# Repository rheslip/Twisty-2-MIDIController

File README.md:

# Twisty 2 MIDI Controller
2nd Generation of my Twisty MIDI controller using Raspberry Pi Pico or Pico 2.

The Twisty 2 MIDI controller has 16 parameter encoders with switches, 16 RGB LEDs, 2 menu encoders, 128x32 pixel OLED display, USB MIDI, TRS MIDI Out, and optional Bluetooth MIDI with Pico W or Pico 2W.
It provides four pages of MIDI controls and fully customizable MIDI messages, encoder ranges, switch functions and LED colors for each control. Text labels can be attached to each control as a visual aid to what the control does. You can save and recall up to 16 controller setups in the Pico's flash memory. STL files for a 3D printed case are provided as well.

Twisty 2 is a completely open source project - source code, KICad schematics and layout, gerber files and enclosure 3D files are in this archive.

Video Overview: https://youtu.be/-W1Gd_hKzS8

Jan 13/2026 - switched MIDI interfaces so they all use the Control Surface library and cleaned up the MIDI interface names - BLE MIDI note on/off works now. Fixed a bug in the init code. 

Jan 25/2026 - added code for a Moog SubHarmonicon like sequencer using the Twisty 2 hardware:

https://www.youtube.com/watch?v=RM_LAcxyHQQ

https://github.com/rheslip/Twisty-2-MIDIController/tree/main/source/Twisty2_Rhythmicon

**Build Guide**

Solder the .1u caps, resistors and the diode. Solder the 16 SK6812 RGB leds making sure the orientation is correct and that the LEDs face the top side of the PCB. Solder the TRS MIDI out jack.

Solder the TSSOP 74HC4067s. I apply a very thin layer of flux to the pads and place the chip so its aligned on the pads. Using a fine tipped soldering iron tack one pin down with solder, adjust as needed and when the part is correctly aligned tack another pin down. Make sure the pins are sitting flat on the pads before you solder the rest. Solder each pin with very fine solder and don't worry about shorts between pins. Once all the pins are soldered examine your work with a magnifier and remove any shorts beween pins with fine solder wick.

Clip the support lugs off all the encoders - there was not enough room in the layout to accomodate them. The encoders have good mechanical support from the enclosure top anyway. The encoders mount from the TOP side of the board and are soldered on the bottom side. You **MUST** solder S2, S6, D2 and D6 **BEFORE** mounting the Pico board. Soldering S2, S6 and then the Pico makes soldering the Pico somewhat easier than soldering all the encoders first.

After all the encoders are soldered, mount the OLED display - temporarily mount the enclosure top as a guide to get the spacing from the display to the top correct.

Hardest part of the build is soldering the three TSSOP 74HC4067 analog MUXes. If encoders aren't working, recheck the soldering on these chips - most faults will be here! Rest of the build is straightforward.

Pico can be mounted with header strips. I used header pins in the corners and short wires to connect the Pico to the PCB which makes the Pico board a lot easier to remove if needed.

Side view of OLED mounting

**Enclosure**

The prototype enclosure was printed on a Bambu P1S with black PLA+ filament. For the most part the stock filament settings were used. Slowing down the first layer speeds by 50% helps with adhesion and finish if you are using a textured build plate. The light pipe holes in the top had to be drilled a bit to fit 1.75mm transparent PETG which was lightly glued to hold it in place. Use small screws to attach the PCB to the standoffs in the enclosure bottom. Slide the enclosure top over the encoder shafts and hold it in place with encoder nuts.

**User Guide**

The top 16 controls (control=encoder+switch) are used to send MIDI CC messages, program change messages or or note on/off messages depending on how the controls are configured. The two extra controls at the bottom are used in conjunction with the OLED display to configure controls, save configurations and recall configurations.

The RGB LEDs associated with each control normally show the state of whatever was last used - encoder as a color and switch states as off or bright white. Encoder LED brightness changes as the control is moved to give a relative idea of the encoder setting. Double click the bottom left control to toggle between showing encoder states and switch states.

Rotate bottom left encoder to move between the 4 pages of controls. Default colors for each page are Red (page 1), Orange (page 2), Green (page ) and Aqua (page 4).

The top line of the OLED display shows the current page, the last used control, its message type and MIDI channel. The larger text below that shows a label if one has been configured and the last value that was sent for that control.

**The Configuration Menu**

Clicking the bottom left control will bring up a configuration menu to edit the last control that was used. The LED for that control will flash to indicate it is selected for editing. To select a different control when in edit mode either press a control switch to choose it or use bottom left encoder to scroll to a different control on the current page.

When in edit mode use the bottom right encoder the scroll through the edit menu items. Click the bottom right control switch to select an item - a "*" character will appear beside the item to indicate it is being edited. Use the bottom right encoder to change the value for the item and click the bottom right encoder switch to select a value.

Click the bottom left encoder again to exit the configuration edit menu.

**Configuration Menu Items:**

**Enc MIDI Ch.** - selects the MIDI channel that the selected encoder will send CC messages on

**Enc CC No.**  - selects the CC number for this encoder. The default CC assignments are 16-31 for page 1, 32-47 for page 2, 48-63 for page 3 and 64-79 for page 4

**Enc Label** - default is "CC". There are approximately 100 common audio terms (e.g. "Level", "Filter", "Track"...) that can be selected as an aid for remembering the function of the control. The label will be displayed instead of the CC number whenever this encoder is used.

**Enc Color** - selects the LED color for this encoder - Red, Orange, Green, Aqua, Blue or Violet. This is useful for grouping control functions by color.

**Enc Min** - minimum CC value that will be sent when the encoder is rotated - defaults to 0

**Enc Max** - maximum CC value that will be sent when the encoder is rotated - defaults to 127. 
**Note** If the minimum setting is higher than the maximum the encoder will reverse ie rotating clockwise sends a lower CC value.

**Switch MIDI Ch.** - selects the MIDI channel that the selected switch will send CC messages on

**Switch Mode** - selects either momentary mode (press for max value, release for min value) or toggle mode (select min or max value on alternate presses)

**Switch Type** - selects switch function:

     **CC** = send CC messages 
 
     **PC** = send program change messages
 
     **Note** = send Note on/off messages
 
     **SetEnc** = when the switch is activated, set the associated encoder on this control to Maxvalue. This provides a quick way to set an encoder to a specific value e.g. set a filter to flat response.
 
**Switch CC No.** - selects the CC number for this switch. This selection only applies when the switch type is send CC messages. The default switch CC assignments are the same as the associated encoder but on MIDI channel 2. 

**Switch Label** - same as encoder label - a memory aid for what the switch does

**Switch Min** - CC, PC or note value sent when the switch changes to its inactive state. defaults to 0

**Switch Max** - CC, PC or note value sent when the switch changes to its active state. defaults to 127. When switch type is SetEnc, sets associated encoder to this value.

**The Save/Load Menu**

Clicking the bottom right encoder enters the save/load menu. Twisty 2 supports saving and loading up to 16 different configurations in the Pico's flash memory.

**Note** You must select an FS size in the Arduino Pico Tools menu - 128K or larger is suggested. The application will automatically format a new FS if it has not been used before. Internally the application uses the LittleFS filesystem and stores configurations as JSON files.

**Save/Load Menu Items:**

**Slot** - selects the slot number 1-16 to save the current configuration to.

**Action** - select Load to load an already saved configuration from the selected slot. Save will save the current configuration to the selected slot. Format will reformat the LittleFS partition - this will ERASE ALL previously saved configurations.

**Confirm** - select Yes to confirm the selected action. The app will **NOT** warn you if you are about to overwrite an existing configuration. If Yes is selected the requested action will be performed, a success/fail message will appear and the Save/load Menu will exit.

**Note** You will get an error message if you attempt to load a configuration slot that hasn't previously been saved to.

To exit the Save/Load menu without changing anything click the bottom left control switch.

**Building the Firmware**

The app was written in Arduino 2.3.7 with the Pico Arduino board support package installed. Select the board type as Pico, Pico 2, Pico 2 or Pico 2W depending on the board you used. The prototype was tested with both a Pico W and a Pico 2 W. In the tools menu select the FS size you want (128k or more is recommended), IP/Bluetooth stack as IPV4 + Bluetooth if you want BLE MIDI, and select the USB stack as Adafruit TinyUSB. This app should not need overclocking since the CPU demands are light.

If you want BLE MIDI, use a Pico W or Pico 2W and uncomment the #define BLUETOOTH directive near the top of the main source file.

Note: I used the Control Surface library because it was the only one I could find that supports BLE MIDI for Arduino Pico. It will give you a warning about supported platforms when you compile but the library does work on the RP2040 and RP2350.

**Library Dependencies**

Adafruit Graphics

Adafruit SSD1306 driver

Adafruit TinyUSB

Adafruit NeoPixel

Arduino MIDI

Arduino JSON  https://arduinojson.org/

Control Surface  https://github.com/tttapa/Control-Surface

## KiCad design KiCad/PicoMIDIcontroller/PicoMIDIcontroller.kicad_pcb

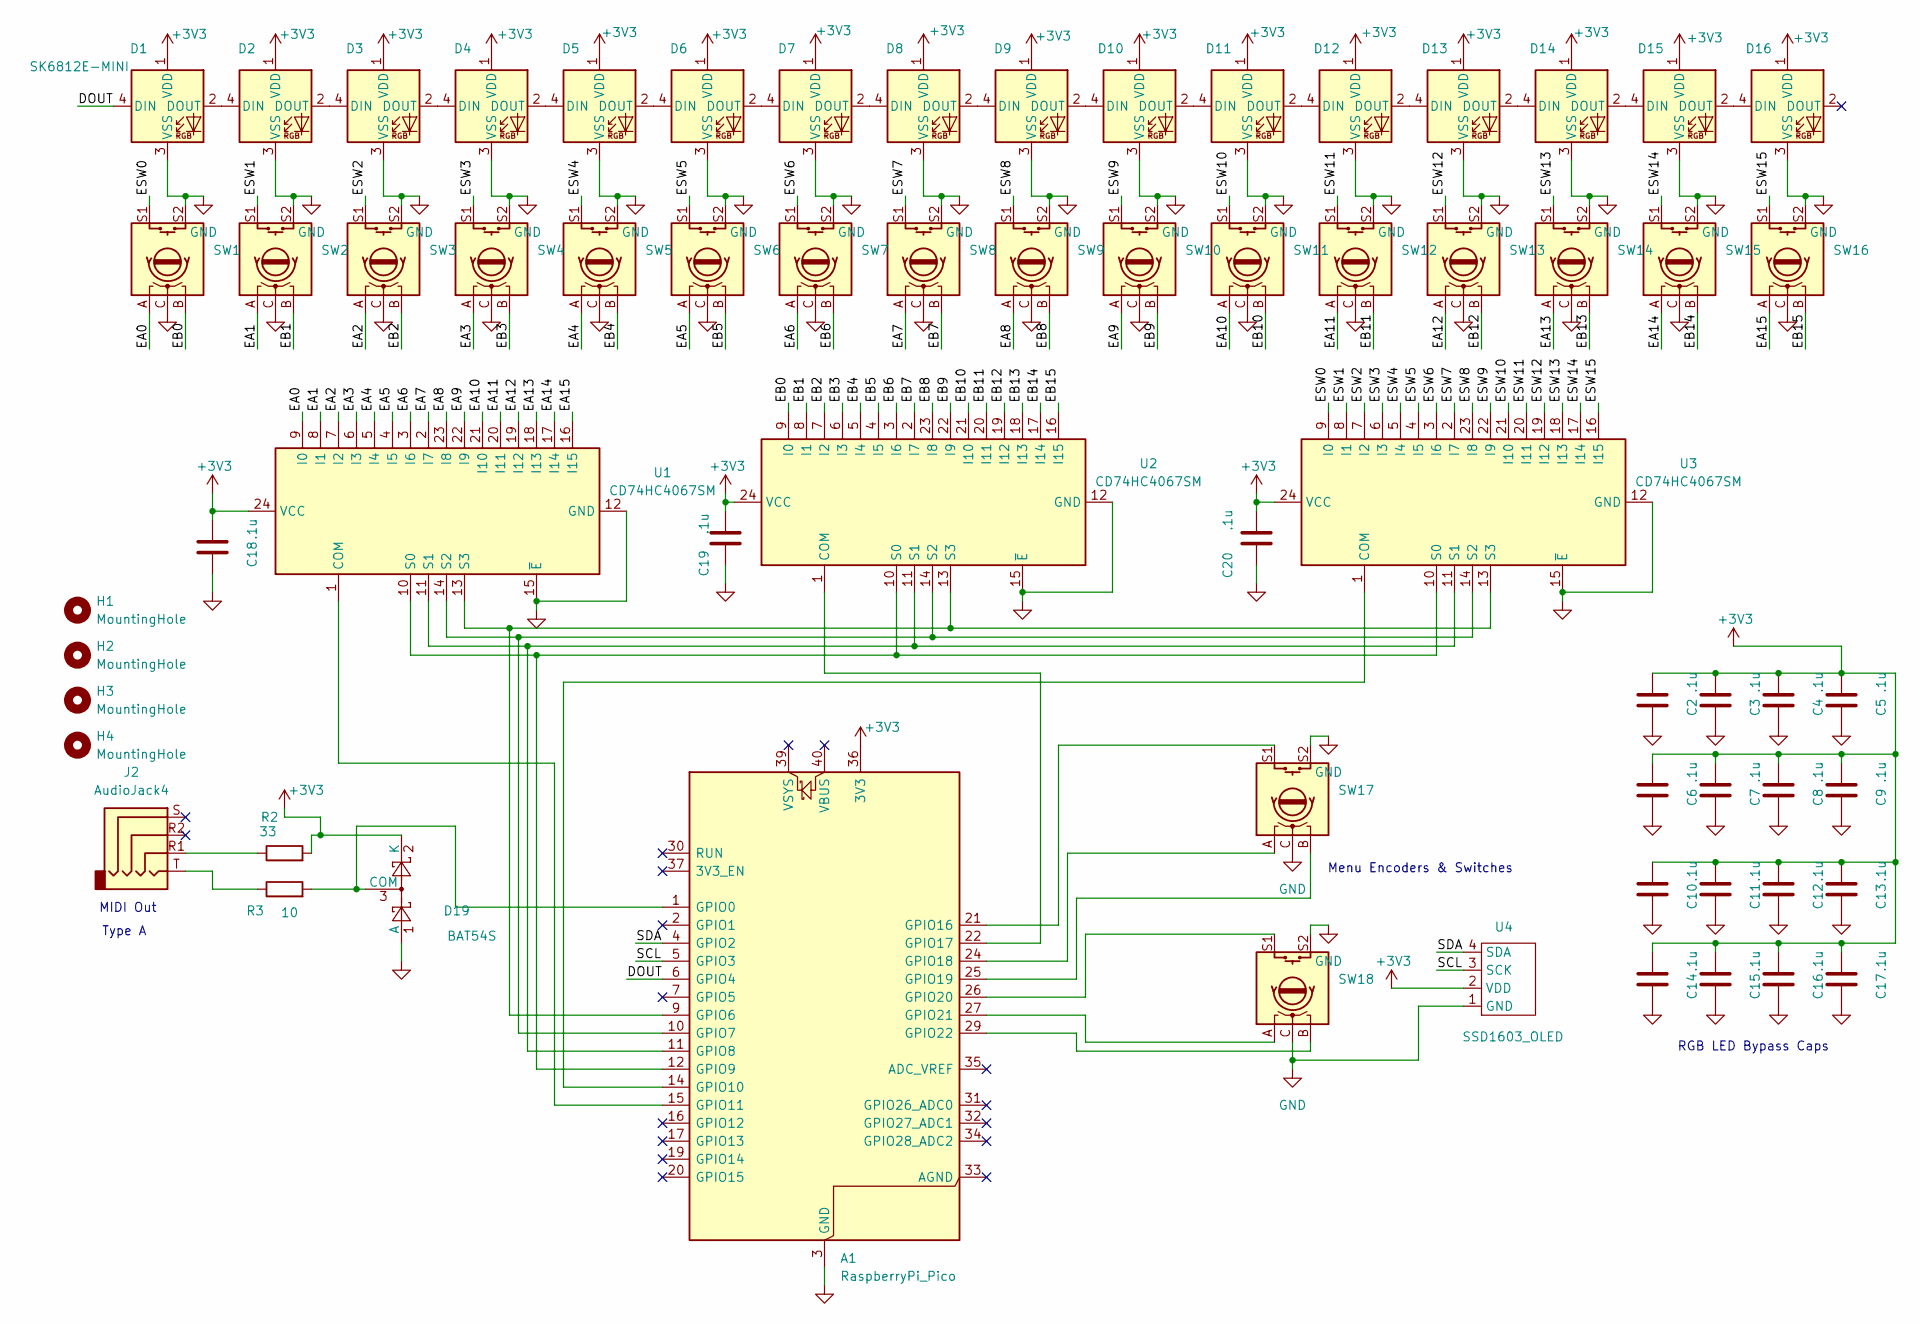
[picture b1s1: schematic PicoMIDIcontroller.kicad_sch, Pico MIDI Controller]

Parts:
A1: RaspberryPi_Pico; RaspberryPi_Pico_Common_nokeepout
C2, C3, C4, C5, C6, C7, C8, C9, C10, C11, C12, C13, C14, C15, C16, C17, C18, C19, C20: .1u; C_0603_1608Metric_Pad1.08x0.95mm_HandSolder
D1, D2, D3, D4, D5, D6, D7, D8, D9, D10, D11, D12, D13, D14, D15, D16: SK6812E-MINI; LED_OPSCO_SK6812_MINI-E_5.0x5.0mm_P3.1mm_rearmount
D19: BAT54S; SOT-23
H1, H2, H3, H4: MountingHole; MountingHole_3.2mm_M3
J2: AudioJack4; Jack_3.5mm_KoreanHropartsElec_PJ-320D-4A_Horizontal
R2: 33; R_0603_1608Metric_Pad0.98x0.95mm_HandSolder
R3: 10; R_0603_1608Metric_Pad0.98x0.95mm_HandSolder
SW1, SW2, SW3, SW4, SW5, SW6, SW7, SW8, SW9, SW10, SW11, SW12, SW13, SW14, SW15, SW16, SW17, SW18: RotaryEncoder_Switch; RotaryEncoder_Alps_EC11E-Switch_Vertical_H20mm_topsolder
U1, U2, U3: CD74HC4067SM; SSOP-24_5.3x8.2mm_P0.65mm
U4: SSD1603_OLED; PinHeader_1x04_P2.54mm_Vertical

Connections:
+3V3: A1.36 (3V3), C2.2, C3.2, C4.2, C5.2, C6.2, C7.2, C8.2, C9.2, C10.2, C11.2, C12.2, C13.2, C14.2, C15.2, C16.2, C17.2, C18.2, C19.2, C20.2, D1.1 (VDD), D2.1 (VDD), D3.1 (VDD), D4.1 (VDD), D5.1 (VDD), D6.1 (VDD), D7.1 (VDD), D8.1 (VDD), D9.1 (VDD), D10.1 (VDD), D11.1 (VDD), D12.1 (VDD), D13.1 (VDD), D14.1 (VDD), D15.1 (VDD), D16.1 (VDD), D19.2 (K), R2.2, U1.24 (VCC), U2.24 (VCC), U3.24 (VCC), U4.2 (VDD); also elsewhere on the board
/DOUT: A1.6 (GPIO4), D1.4 (DIN); also elsewhere on the board
/EA0: SW1.A, U1.9 (I0)
/EA1: SW2.A, U1.8 (I1)
/EA2: SW3.A, U1.7 (I2)
/EA3: SW4.A, U1.6 (I3)
/EA4: SW5.A, U1.5 (I4)
/EA5: SW6.A, U1.4 (I5)
/EA6: SW7.A, U1.3 (I6)
/EA7: SW8.A, U1.2 (I7)
/EA8: SW9.A, U1.23 (I8)
/EA9: SW10.A, U1.22 (I9)
/EA10: SW11.A, U1.21 (I10)
/EA11: SW12.A, U1.20 (I11)
/EA12: SW13.A, U1.19 (I12)
/EA13: SW14.A, U1.18 (I13)
/EA14: SW15.A, U1.17 (I14)
/EA15: SW16.A, U1.16 (I15)
/EB0: SW1.B, U2.9 (I0)
/EB1: SW2.B, U2.8 (I1)
/EB2: SW3.B, U2.7 (I2)
/EB3: SW4.B, U2.6 (I3)
/EB4: SW5.B, U2.5 (I4)
/EB5: SW6.B, U2.4 (I5)
/EB6: SW7.B, U2.3 (I6)
/EB7: SW8.B, U2.2 (I7)
/EB8: SW9.B, U2.23 (I8)
/EB9: SW10.B, U2.22 (I9)
/EB10: SW11.B, U2.21 (I10)
/EB11: SW12.B, U2.20 (I11)
/EB12: SW13.B, U2.19 (I12)
/EB13: SW14.B, U2.18 (I13)
/EB14: SW15.B, U2.17 (I14)
/EB15: SW16.B, U2.16 (I15)
/ESW0: SW1.S1, U3.9 (I0)
/ESW1: SW2.S1, U3.8 (I1)
/ESW2: SW3.S1, U3.7 (I2)
/ESW3: SW4.S1, U3.6 (I3)
/ESW4: SW5.S1, U3.5 (I4)
/ESW5: SW6.S1, U3.4 (I5)
/ESW6: SW7.S1, U3.3 (I6)
/ESW7: SW8.S1, U3.2 (I7)
/ESW8: SW9.S1, U3.23 (I8)
/ESW9: SW10.S1, U3.22 (I9)
/ESW10: SW11.S1, U3.21 (I10)
/ESW11: SW12.S1, U3.20 (I11)
/ESW12: SW13.S1, U3.19 (I12)
/ESW13: SW14.S1, U3.18 (I13)
/ESW14: SW15.S1, U3.17 (I14)
/ESW15: SW16.S1, U3.16 (I15)
/SCL: A1.5 (GPIO3), U4.3 (SCK); also elsewhere on the board
/SDA: A1.4 (GPIO2), U4.4 (SDA); also elsewhere on the board
GND: A1.3 (GND), A1.8 (GND), A1.13 (GND), A1.18 (GND), A1.23 (GND), A1.28 (GND), A1.38 (GND), C2.1, C3.1, C4.1, C5.1, C6.1, C7.1, C8.1, C9.1, C10.1, C11.1, C12.1, C13.1, C14.1, C15.1, C16.1, C17.1, C18.1, C19.1, C20.1, D1.3 (VSS), D2.3 (VSS), D3.3 (VSS), D4.3 (VSS), D5.3 (VSS), D6.3 (VSS), D7.3 (VSS), D8.3 (VSS), D9.3 (VSS), D10.3 (VSS), D11.3 (VSS), D12.3 (VSS), D13.3 (VSS), D14.3 (VSS), D15.3 (VSS), D16.3 (VSS), D19.1 (A), SW1.C, SW1.S2, SW2.C, SW2.S2, SW3.C, SW3.S2, SW4.C, SW4.S2, SW5.C, SW5.S2, SW6.C, SW6.S2, SW7.C, SW7.S2, SW8.C, SW8.S2, SW9.C, SW9.S2, SW10.C, SW10.S2, SW11.C, SW11.S2, SW12.C, SW12.S2, SW13.C, SW13.S2, SW14.C, SW14.S2, SW15.C, SW15.S2, SW16.C, SW16.S2, SW17.C, SW17.S2, SW18.C, SW18.S2, U1.12 (GND), U1.15 (~E), U2.12 (GND), U2.15 (~E), U3.12 (GND), U3.15 (~E), U4.1 (GND); also elsewhere on the board
unnamed 53: A1.1 (GPIO0), D19.3 (COM), R3.2; also elsewhere on the board
unnamed 54: A1.9 (GPIO6), U1.13 (S3), U2.13 (S3), U3.13 (S3); also elsewhere on the board
unnamed 55: A1.10 (GPIO7), U1.14 (S2), U2.14 (S2), U3.14 (S2); also elsewhere on the board
unnamed 56: A1.11 (GPIO8), U1.11 (S1), U2.11 (S1), U3.11 (S1); also elsewhere on the board
unnamed 57: A1.12 (GPIO9), U1.10 (S0), U2.10 (S0), U3.10 (S0); also elsewhere on the board
unnamed 58: A1.14 (GPIO10), U3.1 (COM); also elsewhere on the board
unnamed 59: A1.15 (GPIO11), U1.1 (COM); also elsewhere on the board
unnamed 60: A1.21 (GPIO16), SW17.S1; also elsewhere on the board
unnamed 61: A1.22 (GPIO17), U2.1 (COM); also elsewhere on the board
unnamed 62: A1.24 (GPIO18), SW17.A; also elsewhere on the board
unnamed 63: A1.25 (GPIO19), SW17.B; also elsewhere on the board
unnamed 64: A1.26 (GPIO20), SW18.S1; also elsewhere on the board
unnamed 65: A1.27 (GPIO21), SW18.A; also elsewhere on the board
unnamed 66: A1.29 (GPIO22), SW18.B; also elsewhere on the board
unnamed: D1.2 (DOUT), D2.4 (DIN)
unnamed: D2.2 (DOUT), D3.4 (DIN)
unnamed: D3.2 (DOUT), D4.4 (DIN)
unnamed: D4.2 (DOUT), D5.4 (DIN)
unnamed: D5.2 (DOUT), D6.4 (DIN)
unnamed: D6.2 (DOUT), D7.4 (DIN)
unnamed: D7.2 (DOUT), D8.4 (DIN)
unnamed: D8.2 (DOUT), D9.4 (DIN)
unnamed: D9.2 (DOUT), D10.4 (DIN)
unnamed: D10.2 (DOUT), D11.4 (DIN)
unnamed: D11.2 (DOUT), D12.4 (DIN)
unnamed: D12.2 (DOUT), D13.4 (DIN)
unnamed: D13.2 (DOUT), D14.4 (DIN)
unnamed: D14.2 (DOUT), D15.4 (DIN)
unnamed: D15.2 (DOUT), D16.4 (DIN)
unnamed: J2.R1, R2.1
unnamed: J2.T, R3.1

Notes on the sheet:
MIDI Out
RGB LED Bypass Caps
Menu Encoders & Switches
Type A

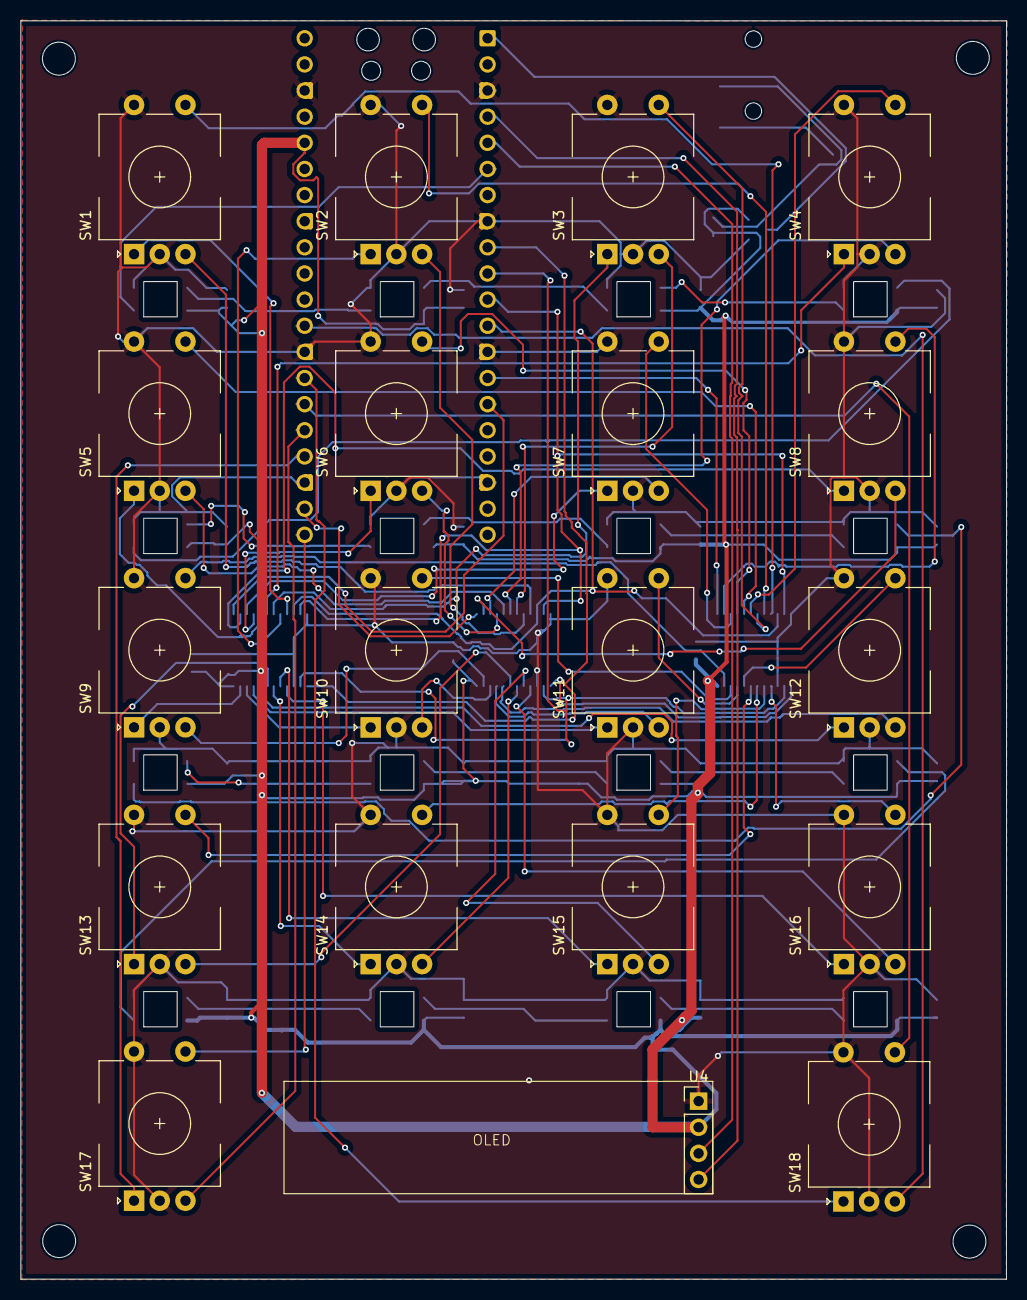
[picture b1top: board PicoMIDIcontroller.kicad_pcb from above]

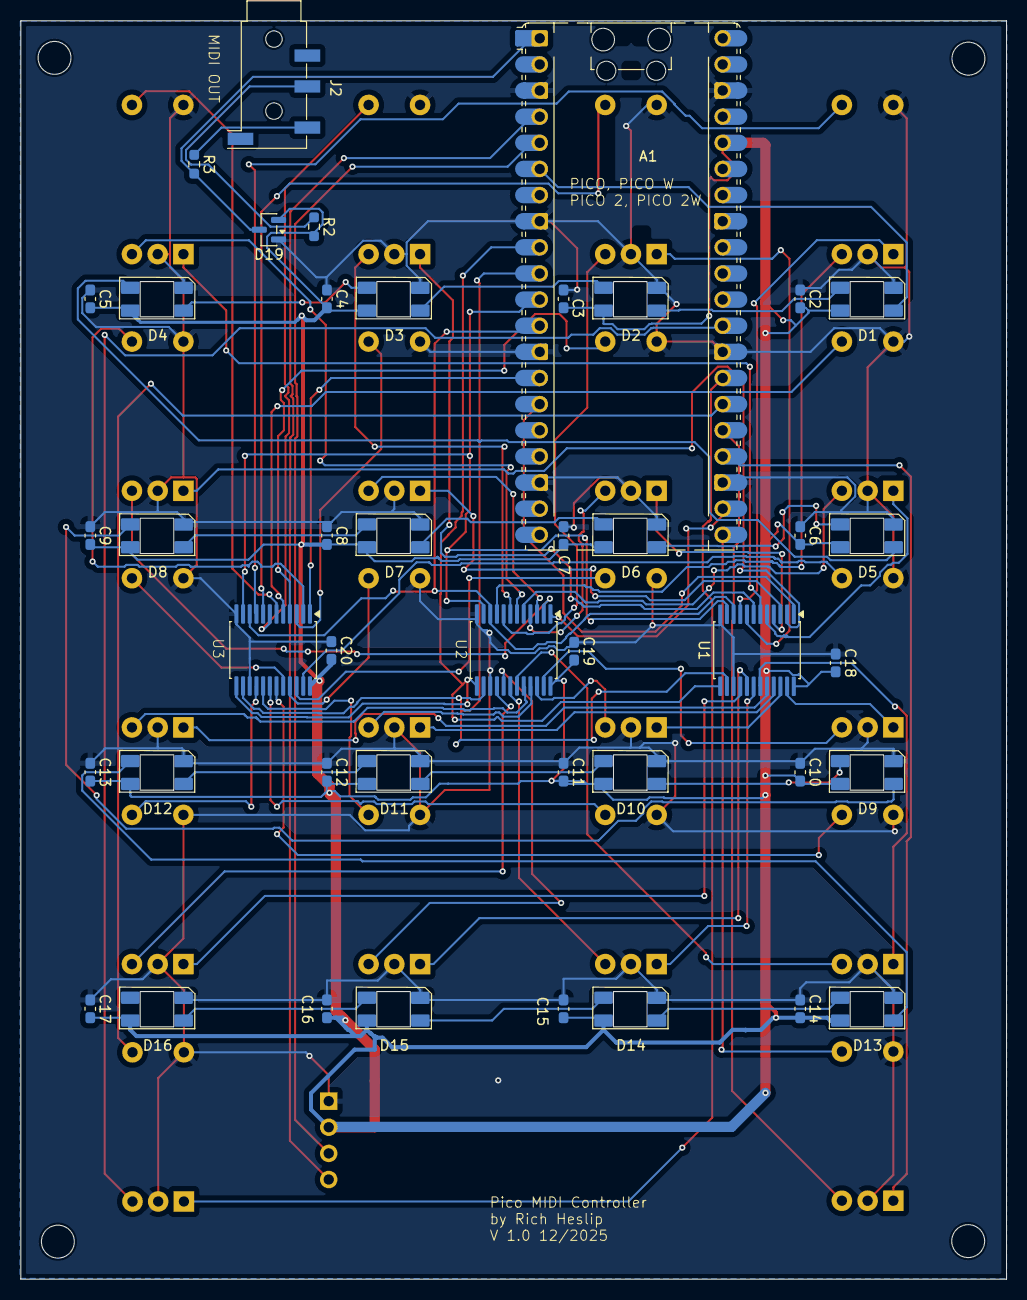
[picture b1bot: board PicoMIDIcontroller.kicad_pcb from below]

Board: 2 copper layers, 95.8 x 122.3 mm, 66 parts (43 on the bottom side), 84 nets.

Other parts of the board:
A1 : RaspberryPi_Pico; RaspberryPi_Pico_Common_nokeepout

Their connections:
+3V3: A1.36 (3V3); also elsewhere on the board
/DOUT: A1.6 (GPIO4); also elsewhere on the board
/SCL: A1.5 (GPIO3); also elsewhere on the board
/SDA: A1.4 (GPIO2); also elsewhere on the board
GND: A1.3 (GND), A1.8 (GND), A1.13 (GND), A1.18 (GND), A1.23 (GND), A1.28 (GND), A1.38 (GND); also elsewhere on the board
unnamed 53: A1.1 (GPIO0); also elsewhere on the board
unnamed 54: A1.9 (GPIO6); also elsewhere on the board
unnamed 55: A1.10 (GPIO7); also elsewhere on the board
unnamed 56: A1.11 (GPIO8); also elsewhere on the board
unnamed 57: A1.12 (GPIO9); also elsewhere on the board
unnamed 58: A1.14 (GPIO10); also elsewhere on the board
unnamed 59: A1.15 (GPIO11); also elsewhere on the board
unnamed 60: A1.21 (GPIO16); also elsewhere on the board
unnamed 61: A1.22 (GPIO17); also elsewhere on the board
unnamed 62: A1.24 (GPIO18); also elsewhere on the board
unnamed 63: A1.25 (GPIO19); also elsewhere on the board
unnamed 64: A1.26 (GPIO20); also elsewhere on the board
unnamed 65: A1.27 (GPIO21); also elsewhere on the board
unnamed 66: A1.29 (GPIO22); also elsewhere on the board

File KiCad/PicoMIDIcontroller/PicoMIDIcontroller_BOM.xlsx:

Reference | Qty | Value | Footprint | Link | Comments | Datasheet
A1 | 1 | RaspberryPi_Pico |  |  | Pico,Pico W, Pico2, Pico 2W | https://datasheets.raspberrypi.com/pico/pico-datasheet.pdf
C2,C3,C4,C5,C6,C7,C8,C9,C10,C11,C12,C13,C14,C15,C16,C17,C18,C19,C20 | 19 | .1u | 0603 |  |  | ~
D1,D2,D3,D4,D5,D6,D7,D8,D9,D10,D11,D12,D13,D14,D15,D16 | 16 | SK6812E-MINI | SK6812_MINI-E_rearmount |  |  | https://cdn-shop.adafruit.com/product-files/2686/SK6812MINI_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
D19 | 1 | BAT54S | SOT-23 |  |  | https://www.diodes.com/assets/Datasheets/ds11005.pdf
H1,H2,H3,H4 | 4 | MountingHole | 3.2mm_M3 |  |  | ~
J2 | 1 | AudioJack4 | PJ-320D-4A_Horizontal |  |  | ~
R2 | 1 | 33 | 0603 |  |  | ~
R3 | 1 | 10 | 0603 |  |  | ~
SW1,SW2,SW3,SW4,SW5,SW6,SW7,SW8,SW9,SW10,SW11,SW12,SW13,SW14,SW15,SW16,SW17,SW18 | 18 | RotaryEncoder_Switch | EC11E-Switch_Vertical |  |  | ~
U1,U2,U3 | 3 | CD74HC4067SM | SSOP-24_5.3x8.2mm |  |  | http://www.ti.com/lit/ds/symlink/cd74hc4067.pdf
U4 | 1 | SSD1603_OLED | 1x04_P2.54mm_Vertical

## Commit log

2026-01-05 Updated source code and added .STL files
    Updated to latest source and added enclosure .STL files
2026-01-05 Update Twisty2.ino
    Removed unused code from loop()
2026-01-13 Changed to Control Surface MIDI
    changed all the MIDI interfaces to use the Control Surface Library. This fixed the bug in ble MIDI send note on/off. Fixed encoder structure initialization bug, made the MID interface names more cons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
2026-01-13 fixed include file for no bluetooth compile
    fixed include files - would not have compiled without bluetooth
2026-01-17 Update PicoMIDIcontroller_BOM.xlsx
    Corrected 4067 package, added links for most parts
2026-01-21 Added enclosure base design with provision for battery power
    Added an enclosure base with cutouts for a USB-C charger module and a switch. The the readme for more details.
2026-01-25 Added PicoRhythmicon Sequencer Code
    PicoRhythmicon is a MIDI sequencer very similar to the Moog Subharmonicon which runs on the Twisty 2 hardware platform.
